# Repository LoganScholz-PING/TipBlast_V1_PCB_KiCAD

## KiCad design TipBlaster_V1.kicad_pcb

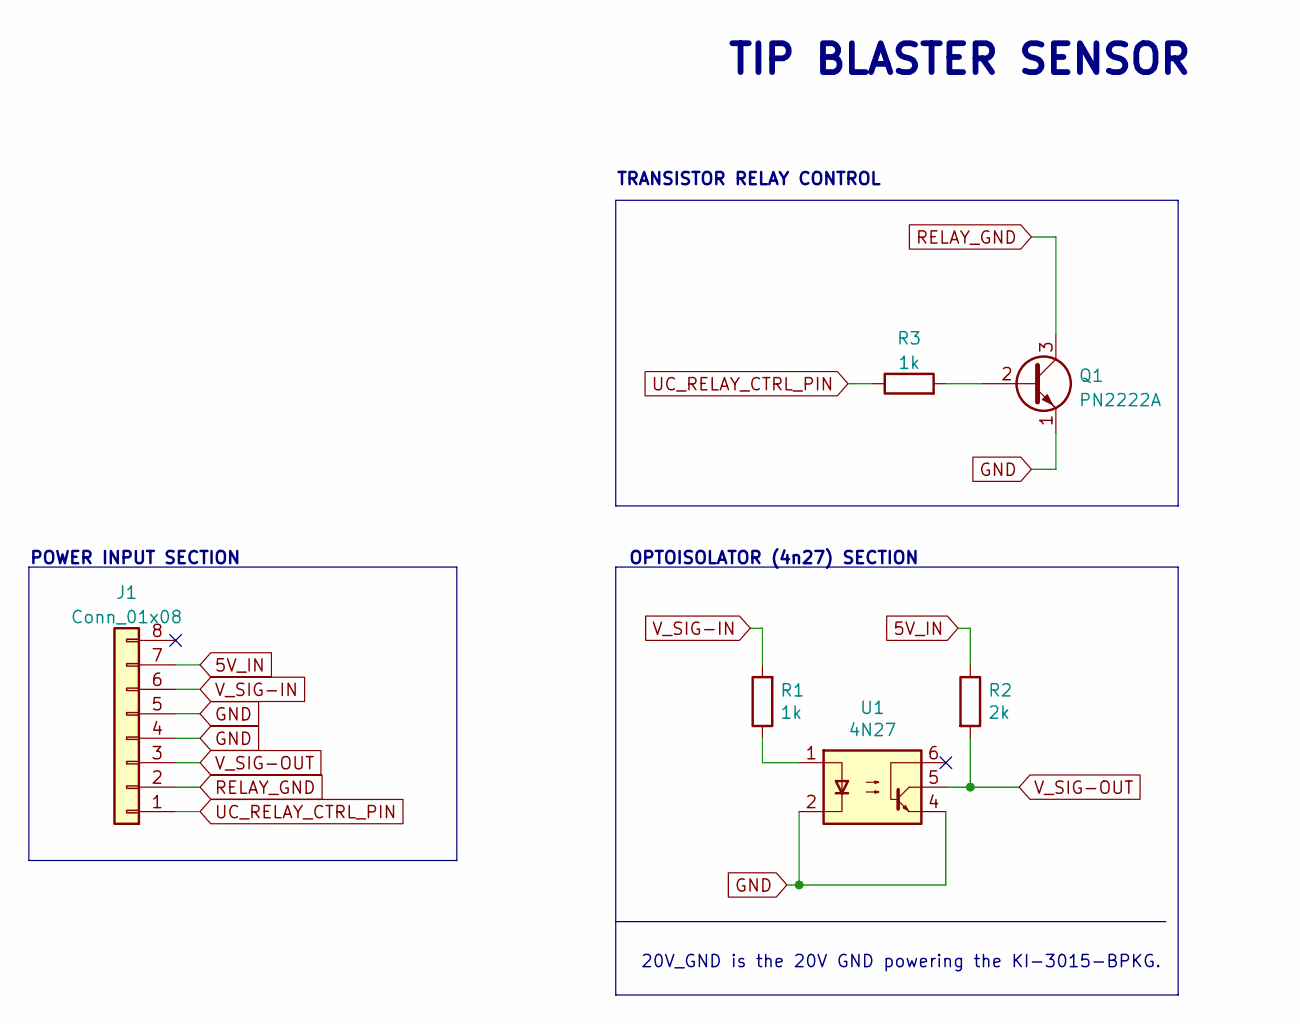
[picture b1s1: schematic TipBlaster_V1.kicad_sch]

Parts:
J1: Conn_01x08; PinHeader_1x08_P2.54mm_Vertical
Q1: PN2222A; TO-92_Inline
R1, R3: 1k; R_Axial_DIN0207_L6.3mm_D2.5mm_P15.24mm_Horizontal
R2: 2k; R_Axial_DIN0207_L6.3mm_D2.5mm_P15.24mm_Horizontal
U1: 4N27; DIP-6_W7.62mm

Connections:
5V_IN: J1.7, R2.1
GND: J1.4, J1.5, Q1.1 (E), U1.2, U1.4
unnamed: Q1.2 (B), R3.2
unnamed: R1.1, U1.1
RELAY_GND: J1.2, Q1.3 (C)
UC_RELAY_CTRL_PIN: J1.1, R3.1
V_SIG-IN: J1.6, R1.2
V_SIG-OUT: J1.3, R2.2, U1.5

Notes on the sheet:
POWER INPUT SECTION
20V_GND is the 20V GND powering the KI-3015-BPKG.
TRANSISTOR RELAY CONTROL
TIP BLASTER SENSOR
OPTOISOLATOR (4n27) SECTION

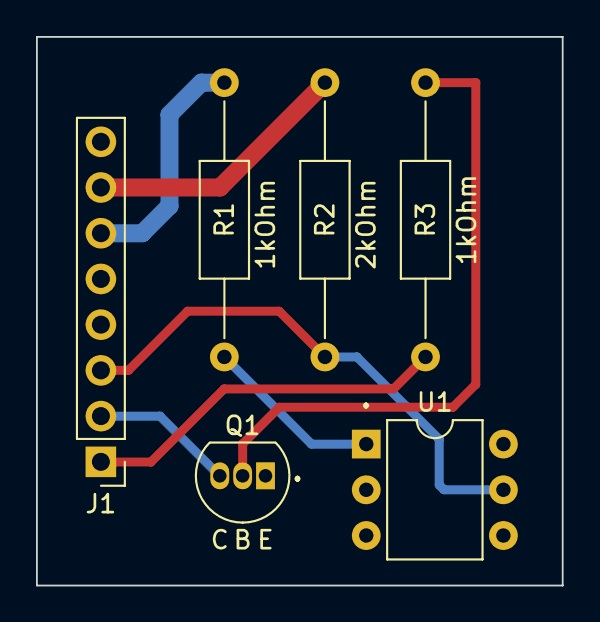
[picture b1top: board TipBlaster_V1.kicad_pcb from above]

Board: 2 copper layers, 29.2 x 30.5 mm, 6 parts (0 on the bottom side), 8 nets.

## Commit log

2022-06-23 finished and sent to JLCPCB
